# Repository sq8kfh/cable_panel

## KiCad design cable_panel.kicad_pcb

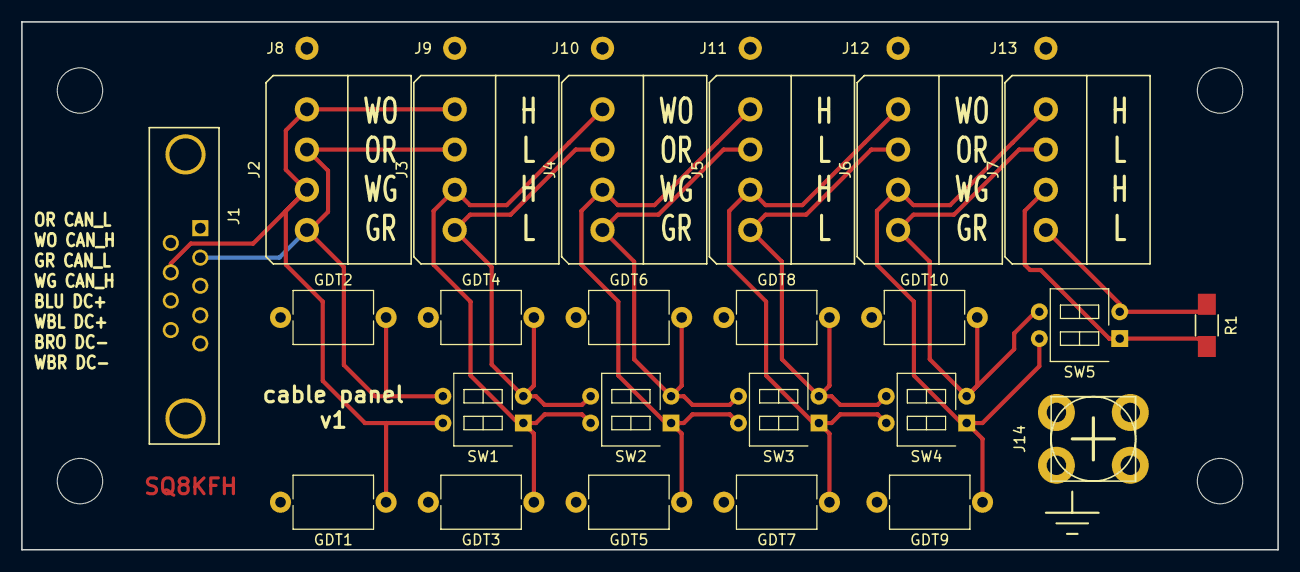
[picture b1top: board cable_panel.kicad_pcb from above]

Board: 2 copper layers, 119.0 x 50.0 mm, 30 parts (0 on the bottom side), 13 nets.

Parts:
GDT1, GDT2, GDT3, GDT4, GDT5, GDT6, GDT7, GDT8, GDT9, GDT10: CG-90L; C_Disc_D7.5mm_W5.0mm_P10.00mm
J1: h9bus; DB9MD
J2: CAN0; PCB-PLUS
J3: CAN1; PCB-PLUS
J4: CAN2; PCB-PLUS
J5: CAN3; PCB-PLUS
J6: CAN4; PCB-PLUS
J7: CAN5; PCB-PLUS
J8: CAN0_SHLD; SolderWirePad_single_1-2mmDrill
J9: CAN1_SHLD; SolderWirePad_single_1-2mmDrill
J10: CAN2_SHLD; SolderWirePad_single_1-2mmDrill
J11: CAN3_SHLD; SolderWirePad_single_1-2mmDrill
J12: CAN4_SHLD; SolderWirePad_single_1-2mmDrill
J13: CAN5_SHLD; SolderWirePad_single_1-2mmDrill
J14: EARTH; Screw_Terminal_M4
R1: 120R; R_1206_HandSoldering
SW1: CAN1; SW_DIP_x2_W7.62mm_Slide_LowProfile
SW2: CAN2; SW_DIP_x2_W7.62mm_Slide_LowProfile
SW3: CAN3; SW_DIP_x2_W7.62mm_Slide_LowProfile
SW4: CAN4; SW_DIP_x2_W7.62mm_Slide_LowProfile
SW5: CAN5; SW_DIP_x2_W7.62mm_Slide_LowProfile

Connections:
/CAN0+: GDT1.1, J1.7, J2.1, J2.3, J3.1, SW1.4
/CAN0-: GDT2.2, J1.2, J2.2, J2.4, J3.2, SW1.3
/CAN1+: GDT3.1, J3.3, J4.1, SW1.1, SW2.4
/CAN1-: GDT4.2, J3.4, J4.2, SW1.2, SW2.3
/CAN2+: GDT5.1, J4.3, J5.1, SW2.1, SW3.4
/CAN2-: GDT6.2, J4.4, J5.2, SW2.2, SW3.3
/CAN3+: GDT7.1, J5.3, J6.1, SW3.1, SW4.4
/CAN3-: GDT8.2, J5.4, J6.2, SW3.2, SW4.3
/CAN4+: GDT9.1, J6.3, J7.1, SW4.1, SW5.4
/CAN4-: GDT10.2, J6.4, J7.2, SW4.2, SW5.3
/CAN5+: J7.3, R1.2, SW5.1
/CAN5-: J7.4, R1.1, SW5.2
Earth: GDT1.2, GDT2.1, GDT3.2, GDT4.1, GDT5.2, GDT6.1, GDT7.2, GDT8.1, GDT9.2, GDT10.1, J1.0, J1.3, J1.5, J8.1, J9.1, J10.1, J11.1, J12.1, J13.1, J14.1

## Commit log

2019-05-04 init
2019-05-05 added missing files
2019-05-05 fixed a silkscreen layer
2019-05-05 added gerber
2019-05-05 added a author name to a schema
2019-05-09 v1.0rc
2019-05-09 name,version fix
